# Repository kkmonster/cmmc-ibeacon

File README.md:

-cmmc-ibeacon
=============

PCB BLE-ibeacon Mudule  v1

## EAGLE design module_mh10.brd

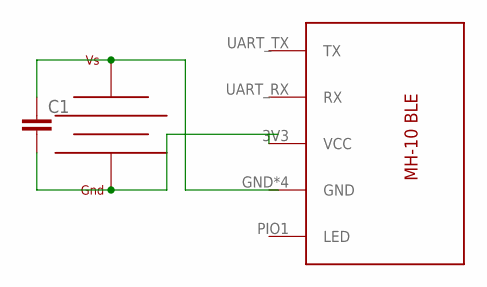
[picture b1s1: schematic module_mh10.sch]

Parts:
C1: C5/2.5; C5B2.5
U$1: HM-10
U$2: CR2032; CR2032_V

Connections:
unnamed: C1.2, U$2.GND
unnamed: C1.1, U$2.VSS

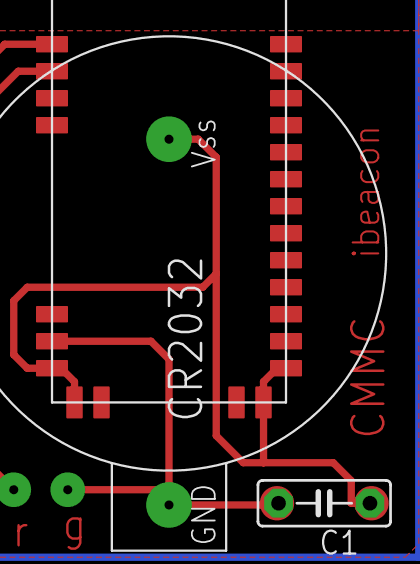
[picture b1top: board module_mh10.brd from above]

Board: 2 copper layers, 3 parts (0 on the bottom side), 2 nets.

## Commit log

2014-08-16 original v1
2014-08-16 add pdf file.
